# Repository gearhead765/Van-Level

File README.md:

# Van Level

## Overview

ESP32 Based digital level to display leveling information for a camper van. This originally started as an ESPHome application however, the requirement to have Home Assistant running on your phone or tablet in order to see the leveling information was cumbersome.  It was decided that displaying the information on a simple web page, instead of a Home Assistant Lovelace overview, would be much easier to use.  However, there is also a [Home Assistant Dashboard](HOMEASSISTANT.md) setup available.

This app displays a simple webpage with a graphic of a camper van showing the amount of wheel lift (blocking) needed under each tire to level the van.  Included is the *Van Level* app, Kicad PCB files, and Solidworks files to modify a Hammond enclosure to contain the project.

## Product Images

## Project Structure

```
├── CAD Model/                       # SolidWorks 3D model of the board and Hammond enclosure
├── Notes/                           # Datasheets and component references
├── Van_Level_App/Van_Level          # Arduino ESP32 source code
│                 ├── data/          # App's LittleFS website
│                 │   └── images/
│                 └── HomeAssistant/ # RESTful Lovelace card for Home Assistant
├── Van_Level_PCB/                   # Kicad board files
│   └── Component Models/            # STEP files of board components
├── HARDWARE.md                      # Hardware specifications and components
├── HOMEASISTANT.md                  # Integrating with Home Assistant
├── README.md                        # This file
└── SOFTWARE.md                      # Software description
```

## [Hardware](HARDWARE.md)

## [Software](SOFTWARE.md)

## [Home Assistant](HOMEASSISTANT.md)

## Features
This application uses an ESP23 to read acceleration values from an IMU to calculate the pitch and roll angles for a vehicle.  A little trig is used to convert these angles into block heights needed to level the vehicle. The resulting information in presented graphically via a self-hosted webpage and are also made available via a RESTful API resource.

The Wifi supports a standard network client, using either DHCP or static network setup, as well as a local Access Point for connecting directly to the device without a local network.

The leveling information can be viewed using any browser that supports Javascript. The webpage displays an image of a van, and a value next to each wheel requiring blocking.  The rounding of the height values presented can be adjusted to correspond to your leveling block height.  If you have 1" blocks, the rounding value can be set to change in 1" increments.  Additionally, the image background will change to green when the vehicle is level within a user specified range.

The van image can be changed to reflect your particular vehicle model and color, and the vehicle's wheelbase and track measurements can be edited to fit your particular van.  Details on these features are in [Software](SOFTWARE.md).

## Getting Started

### 1. Hardware Setup
1. Connect the ESP32 board to 12V DC power via connector C1 observing correct polarity.
1. Connect to the built-in Access Point by opening your phone or computer Wifi Settings and selecting the `VAN_LEVEL` access point.
1. The default password for the access point is `12345678`.
1. The default name `VAN_LEVEL` and password `12345678` can be changed later.
1. Open the app webpage in any browser by navigating to the hotspot address `192.168.4.1`.
1. Your browser window should look something like this:
<br>

### 2. The Main Display
1. The image above is the standard display in portrait mode.  It will auto rotate for landscape and both views support your browser's `Dark Mode` setting.
1. Next to each wheel location is the number of inches of blocking necessary to level your camper.  If no blocking is needed for a particular wheel, the height for that wheel will be hidden.  The granularity for these values is user selectable (i.e. to match your block height).
1. Centered on the van image, is the status information for your vehicle, including the current pitch and roll values.  If communication with the app is impaired, the status information will flash to indicate aging wheel lift data.  If communication is impaired for a significant amount of time, the status text will flash faster and the wheel lift data will become grayed out.
1. If the pitch and roll values are within user defined tolerances, the background will change to green signifying the van is level.  There is an example of this at the begining of this document.

### 3. AP Configuration
1. To connect the *Van Level* app to your local network, or to change the default access point address, name, and/or password, we need to connect to the configuration page.  Navigate your browser to `192.168.4.1/setup`.
1. You will be asked for a login name and password.  These are the same as the AP name and password initially, and can be easily changed later.
<br>
1. After pressing `Sign in`, your browser should now be displaying the app setup page with the `status` tab selected:
<br>
1. On this page, you can change the Access Point name, IP address, and password.
1. If you make changes to any of the AP settings, after hitting `Apply`, you will need to switch to the `Other` tab and select `Reboot` to enable the changes.
1. The setup page authorization name and password **are the same** as the AP name and password.  If you change the AP name and/or password on this page, remember the values so you can log into the device configuration later.
1. There will be an alert at the top of the page if you are using the default name and/or password.  For security reasons, it is best to change these to something uniquely yours.
1. If you forget your AP name or password, you will no longer be able to log into the `setup` page to make changes.  If this happens, you can reset the App to the original defaults by holding down the 'Boot' button on the ESP32 board for 5 seconds while the device reboots.

### 4. Network Configuration
1. The `Network` tab allows you to connect the *Van Level* app to your local network.  Pressing the `Scan Wi-Fi` button will search for all available access points.  When the scanning is finished, selecting the `Nearby WLAN` dropdown will present a list of all APs found allowing you to select one.
<br>
1. Enter the WiFi password for this network.
1. You can now select DHCP or Static network configuration.  After you have made your selections and filled in the network password, click `Apply`.  Changes are automatic and you do not need to restart the device.
1. You can switch back to the `Status` tab and verify your selected WiFi connection.

### 5. Calibration

1. If the pitch or roll values of your van are not `0` when the van is level, you can enter the opposite amount here to tare the display.  For example, if your van shows +1.0° pitch when level, enter -1.0 in the pitch offset box.
1. Depending on how you mount the Van Level hardware, your pitch and roll values might move in the opposite direction.  Positive pitch should be nose up, and positive roll should be clockwise looking forward (i.e. drivers side higher than the passenger side).  Select `Reverse Direction` if either of your values are opposite of this standard.
1. The `Filter Alpha` setting controls the amount of *dampening* on the pitch and roll readings. I have found a setting of `0.10` seems to be a good compromise between responsiveness and reading jitter.
1. The `Block Size` setting should be set to the smallest block thickness in your stash.  If you have plywood blocks, you might set this to `0.5` [1/2"].  If you use 2 by 12 blocks then you would set this to `1.5` [the nominal thickness of 1.5"].  Many aftermarked plastic block sets are 1" increments.
1. Finally, pitch and roll tolerance is a subjective measure of what you consider *good enough*.  If your vehicle's pitch and roll angles are below these settings, the web page background will turn green signaling *level*.  For reference, on my van with a 148" wheelbase and 68" track, the table below shows various block heights and the corresponding angle values.  I have my tolerances set to slightly less than the 1" block angles since I consider anything less than 1" *good enough*.

    | Block Height (inches) | Pitch Angle Change | Roll Angle Change |
    |----------------------|-------------------|-----------------|
    | 0.25" (1/4) | 0.097° | 0.211° |
    | 0.50" (1/2) | 0.193° | 0.421° |
    | 0.75" (3/4) | 0.290° | 0.631° |
    | **1.00" (1)** | **0.387°** | **0.843°** |
    | 1.25" | 0.483° | 1.052° |
    | 1.50" (1-1/2) | 0.580° | 1.261° |

1. Click the `Apply` button to immediately apply these changes.

### 6. Other

1.  `Reboot` will restart the Van Level device retaining all of your current settings.
1.  `Reset` will clear your stored Wifi network information and restore the default AP captive portal name and password.  **Make sure** this is what you want before pressing `Reset`.  If you have forgotten your AP name and password and can no longer access the configuration page because of this, it is possible to reset the hardware physically.  This process is discussed in [Software](SOFTWARE.md).
1. Selecting `Update Firmware / File System Upload` will allow *Over The Air* updating of the program and webpages.  See [Software](SOFTWARE.md) for more information on this process.
<br>

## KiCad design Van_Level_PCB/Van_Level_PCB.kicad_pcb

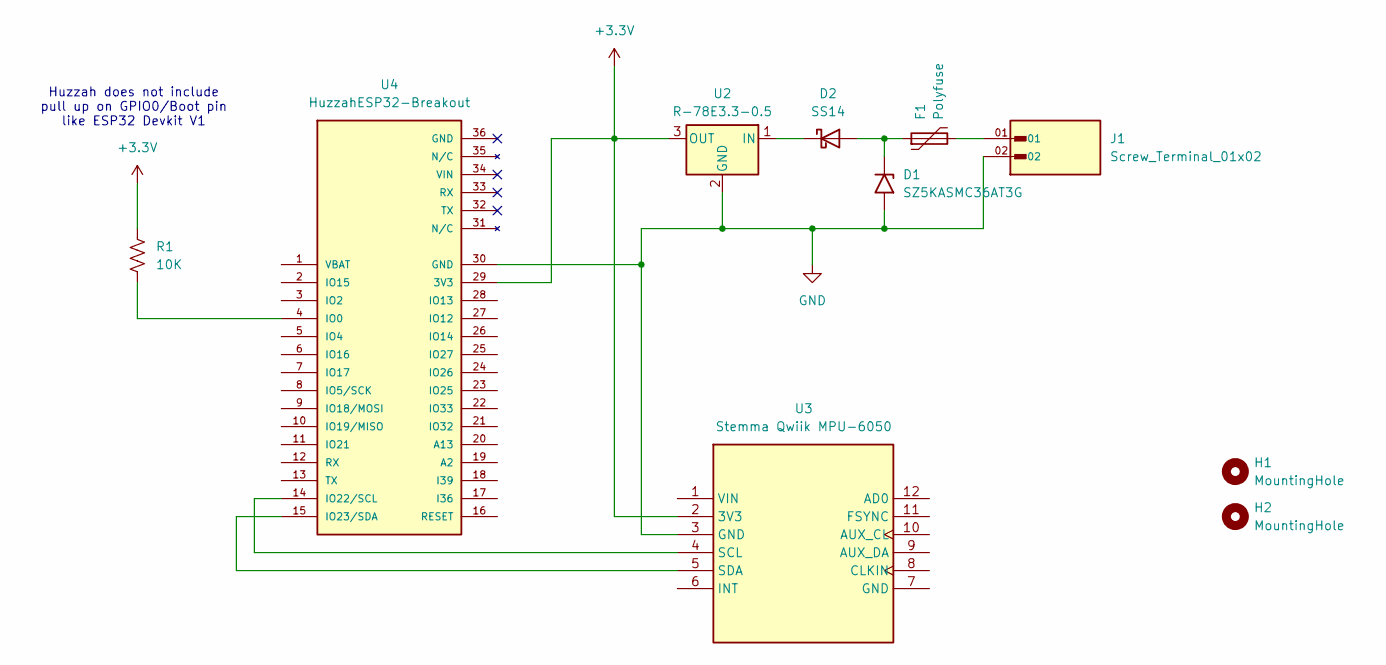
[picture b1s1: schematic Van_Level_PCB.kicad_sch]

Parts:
D1: SZ5KASMC36AT3G; ST_D_SMC
D2: SS14; D_SMA
F1: Polyfuse; Fuse_1812_4532Metric_Pad1.30x3.40mm_HandSolder
H1, H2: MountingHole; MountingHole_2.5mm
J1: Screw_Terminal_01x02; PHOENIX_1844210; PARTREV 02.08.2023
R1: 10K; R_0805_2012Metric_Pad1.20x1.40mm_HandSolder
U2: R-78E3.3-0.5; Converter_DCDC_RECOM_R-78E-0.5_THT_Horizontal
U3: Stemma Qwiik MPU-6050; Stemma Qwiik 0.5_ x 0.8_ 6+6-pin
U4: HuzzahESP32-Breakout; HUZZAH32_Breakout; PARTREV N/A

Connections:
+3.3V: R1.1, U2.3 (OUT), U3.2 (3V3), U4.29 (3V3)
GND: D1.2 (A2), J1.02, U2.2 (GND), U3.3 (GND), U4.30 (GND)
unnamed: D1.1 (A1), D2.2 (A), F1.1
unnamed: D2.1 (K), U2.1 (IN)
unnamed: F1.2, J1.01
unnamed: U3.4 (SCL), U4.14 (IO22/SCL)
unnamed: U3.5 (SDA), U4.15 (IO23/SDA)
unnamed: R1.2, U4.4 (IO0)

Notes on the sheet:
Huzzah does not include pull up on GPIO0/Boot pin like ESP32 Devkit V1

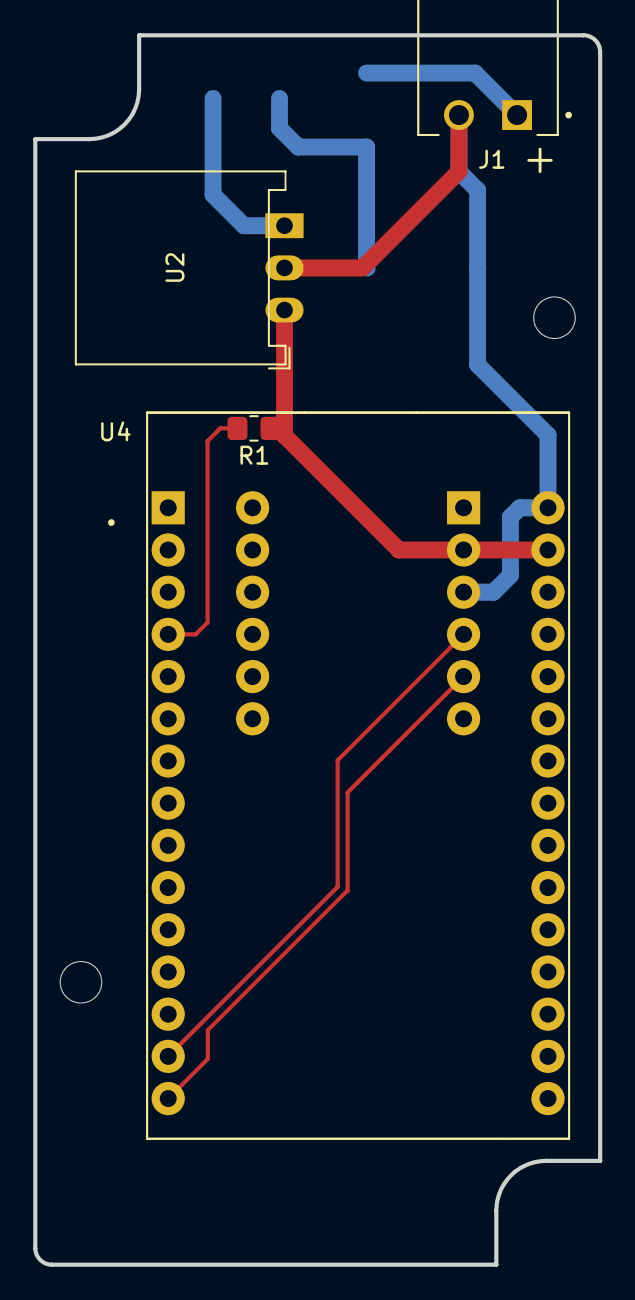
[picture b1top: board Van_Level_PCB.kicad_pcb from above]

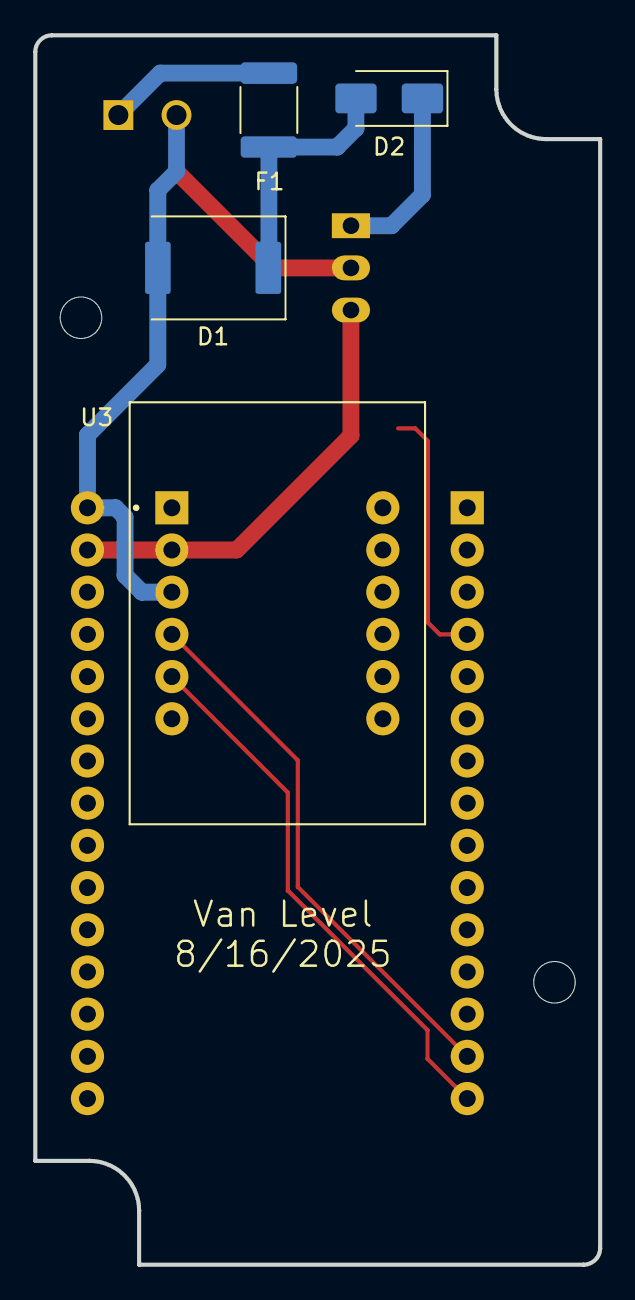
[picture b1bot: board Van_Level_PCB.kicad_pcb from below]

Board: 2 copper layers, 34.0 x 74.0 mm, 10 parts (4 on the bottom side), 8 nets.

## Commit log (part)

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2026-04-30 Initial commit of source
2026-04-30 Removed Kicad backups folder
2026-04-30 start on images and markdown docs
2026-05-01 Fixed POST errors in html, pullup issues in reset function
    Boards without pullup resistors on GPIO0 would reset WiFi credentials every restart. Provided option in code to use INPUT or INPUT_PULLUP depending on dev board used.
    POST was being used for credential settings from setup.html, but was actually appending arguments like GET.
2026-05-01 changed display fraction to 1/2
    Changed the granularity on the leveling amounts to 1/2" increments. Made the YAML code a little easier to change in the future. Down from 24 places to just 4 instances.
2026-05-01 fixed comment char, bumped version
2026-05-02 update HA yaml
    HA deprecated `platform: template`. Files updated to new top level `template:`.
    Added version to dashboard display.
2026-05-04 moved alpha and fraction to setup values
    changed hardcoded smoothing alpha and leveling block fraction values, to setup/calibration values
2026-05-04 documentation
    still working on getting the documentation ready to publish
2026-05-05 revised images and updated documentation
2026-05-05 Create LICENSE
2026-05-05 change LICENSE to LICENSE.md
